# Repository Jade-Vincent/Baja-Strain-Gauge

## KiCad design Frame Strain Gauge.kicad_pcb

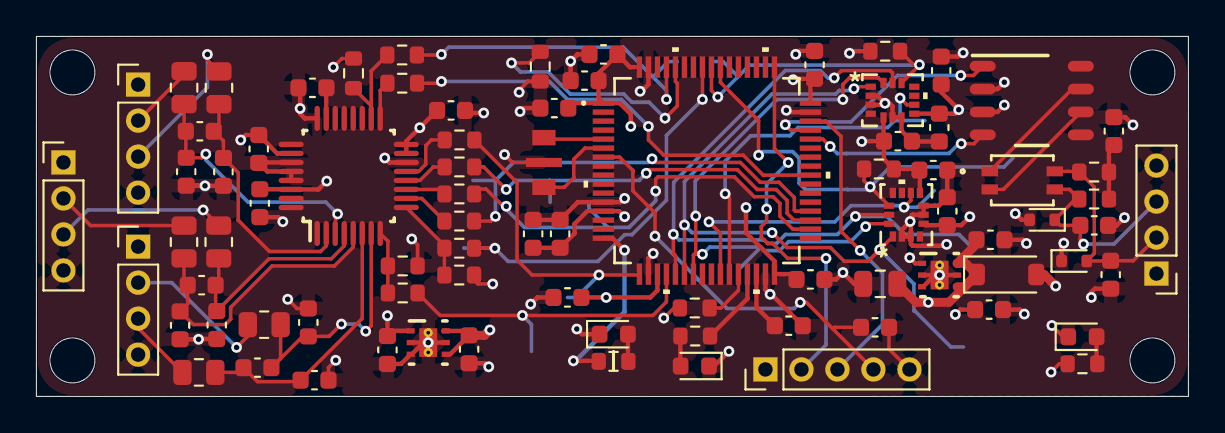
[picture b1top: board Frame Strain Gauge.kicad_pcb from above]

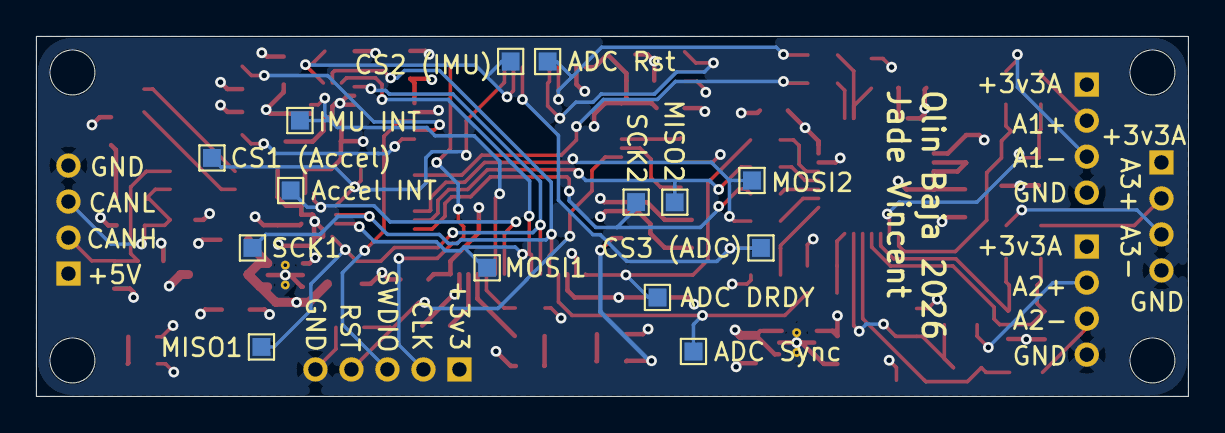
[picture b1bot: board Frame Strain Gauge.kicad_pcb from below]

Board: 4 copper layers, 64.0 x 20.0 mm, 96 parts (14 on the bottom side), 61 nets.

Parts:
ADC DRDY: TestPoint; TestPoint_Pad_1.0x1.0mm
ADC Rst: TestPoint; TestPoint_Pad_1.0x1.0mm
ADC Sync: TestPoint; TestPoint_Pad_1.0x1.0mm
Accel INT: TestPoint; TestPoint_Pad_1.0x1.0mm
C1, C2, C3, C4, C19: 100nF; C_0603_1608Metric
C5: 330 nF; C_0603_1608Metric
C6, C7, C11: 0.1uF; C_0603_1608Metric
C8, C9, C10, C12, C13, C14: 0.01uF; C_0603_1608Metric
C15: 0.1 uF; C_0603_1608Metric
C16, C34, C37, C38, C46, C47, C48, C49: 100 nF; C_0603_1608Metric
C17, C35, C36, C43: 1 uF; C_0603_1608Metric
C18, C33, C44: 2.2 uF; C_0603_1608Metric
C31: 4.7 uF; C_0603_1608Metric
C40, C41: 10 pF; C_0603_1608Metric
C42: 4.7 nF; C_0603_1608Metric
C45: 10 uF; C_0805_2012Metric
CS1 (Accel), CS2 (IMU), CS3 (ADC): TestPoint; TestPoint_Pad_1.0x1.0mm
D1, D2, D3: LED; LED_0603_1608Metric
D4, D5: 12v; D_SOD-523
D6: D_Schottky; D_SOD-123
IMU INT: TestPoint; TestPoint_Pad_1.0x1.0mm
J1: Conn_01x05_Pin; PinHeader_1x05_P2.00mm_Vertical
J4: CAN Header; PinHeader_1x04_P2.00mm_Vertical
J5: Strain Gauge 3 (Shear); PinHeader_1x04_P2.00mm_Vertical
J6: Strain Gauge 2 (Torsion); PinHeader_1x04_P2.00mm_Vertical
J7: Strain Gauge 1 (Axial Load); PinHeader_1x04_P2.00mm_Vertical
MISO1, MISO2: TestPoint; TestPoint_Pad_1.0x1.0mm
MOSI1, MOSI2: TestPoint; TestPoint_Pad_1.0x1.0mm
R1, R2, R5, R6, R7, R8, R9: 10k; R_0603_1608Metric
R10, R17, R18, R19, R20, R21, R22, R28: 47; R_0603_1608Metric
R11, R12, R13, R14, R15, R16: 500; R_0805_2012Metric
R23, R24, R25: 680; R_0603_1608Metric
R26, R27: 60; R_0603_1608Metric
SCK1, SCK2: TestPoint; TestPoint_Pad_1.0x1.0mm
U1: CSTNE8M00GH5C000R0; CSTN_CAP_3P2X1P3_MUR
U2: LSM6DSOXTR; LGA-14L_STM
U3: IIS3DWBTR; LGA-14L_2P5X3X0P83_STM
U4: ADS124S08IPBSR; PBS0032A_N
U5, U8: TPS7A2633DRVR; DRV0006A
U6: TCAN332GDR; D0008A_N
U7: ACT1210-510-2P-TL00; CHOKE_10-2P-TL00_TDK
U10: STM32F412RGT6; LQFP64-10x10mm

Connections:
+3V3: C1.1, C2.1, C3.1, C4.1, C15.2, C18.1, C19.1, C31.1, C34.2, C35.2, C38.1, C46.1, C47.1, C48.1, C49.1, J1.1, R1.2, R5.1, R6.1, R9.1, R23.2, U2.5 (VDDIO), U2.8 (VDD), U3.5 (VDD_IO), U3.8 (VDD), U4.15 (IOVDD), U4.16 (DVDD), U5.1 (OUT), U6.3 (VCC), U10.1 (VBAT), U10.13 (VDDA/VREF+), U10.19 (VDD), U10.32 (VDD), U10.48 (VDD), U10.64 (VDD)
+3V3A: C5.2, C16.1, C44.1, J5.1, J6.1, J7.1, U4.26 (AVDD), U4.30 (REFP0), U8.1 (OUT)
+5V: C17.1, C43.1, C45.2, D6.1 (K), U5.4 (EN), U5.6 (IN), U8.4 (EN), U8.6 (IN)
/Axial+: J7.2, R11.1
/Axial-: J7.3, R12.1
/CAN RXD: U6.4 (RXD), U10.44 (PA11)
/CAN TXD: U6.1 (TXD), U10.45 (PA12)
/CANH: C40.1, D5.2 (A2), J4.2, R26.1, U7.4
/CANL: C41.1, D4.1 (A1), J4.3, R27.2, U7.3
/CS1 IIS3DWBTR: CS1 (Accel).1 (1_1), R5.2, U3.12 (CS), U10.55 (PB3)
/CS2 LSM6DSOXTR: CS2 (IMU).1 (1_1), R6.2, U2.12 (CS), U10.56 (PB4)
/CS3 ADS124S08IPBSR: CS3 (ADC).1 (1_1), R20.1, U10.57 (PB5)
/DRDY ADS124S08IPBSR: ADC DRDY.1 (1_1), R18.1, U10.17 (PA3)
/INT IIS3DWBTR: Accel INT.1 (1_1), U3.9 (INT2), U10.26 (PB0)
/INT LSM6DSOXTR: IMU INT.1 (1_1), U2.9 (INT2), U10.27 (PB1)
/MCO: R28.1, U10.40 (PC9)
/NRST: C37.1, J1.4, U10.7 (NRST)
/Reset ADS124S08IPBSR: ADC Rst.1 (1_1), R10.1, U10.61 (PB8)
/Resonator Input: U1.1, U10.5 (PH0-OSC_IN)
/Resonator Output: U1.3, U10.6 (PH1)
/SPI 1 MISO: MISO1.1 (1_1), U2.1 (SDO/SA0), U3.1 (SDO/SA0), U10.22 (PA6)
/SPI 1 MOSI: MOSI1.1 (1_1), U2.14 (SDA), U3.14 (SDI/SDO/SDA), U10.23 (PA7)
/SPI 1 SCK: SCK1.1 (1_1), U2.13 (SCL), U3.13 (SPC/SCL), U10.21 (PA5)
/SPI 2 MISO: MISO2.1 (1_1), R19.1, U10.35 (PB14)
/SPI 2 MOSI: MOSI2.1 (1_1), R21.1, U10.36 (PB15)
/SPI 2 SCK: R22.1, SCK2.1 (1_1), U10.34 (PB13)
/SWCLK: J1.2, U10.49 (PA14)
/SWDIO: J1.3, U10.46 (PA13)
/Shear+: J5.2, R15.1
/Shear-: J5.3, R16.1
/Start/Sync ADS124S08IPBSR: ADC Sync.1 (1_1), R17.1, U10.20 (PA4)
/Torsion+: J6.2, R13.1
/Torsion-: J6.3, R14.1
GND: C1.2, C2.2, C3.2, C4.2, C5.1, C8.2, C9.1, C10.1, C12.2, C13.1, C14.2, C15.1, C16.2, C17.2, C18.2, C19.2, C31.2, C33.2, C34.1, C35.1, C36.2, C37.2, C38.2, C40.2, C41.2, C42.2, C43.2, C44.2, C45.1, C46.2, C47.2, C48.2, C49.2, D1.1 (K), D2.1 (K), D3.1 (K), D4.2 (A2), D5.1 (A1), J1.5, J4.4, J5.4, J6.4, J7.4, R2.2, R7.2, R8.1, U1.2, U2.2 (SDX), U2.3 (SCX), U2.6 (GND), U2.7 (GND), U3.2 (RES), U3.3 (RES), U3.6 (GND), U3.7 (GND), U4.14 (DGND), U4.24 (REFCOM), U4.27 (AVSS), U4.28 (AVSS-SW), U4.29 (REFN0), U5.2 (FB_NC), U5.3 (PG), U5.5 (GND), U5.7 (PAD), U5.V, U6.2 (GND), U8.2 (FB_NC), U8.3 (PG), U8.5 (GND), U8.7 (PAD), U8.V, U10.12 (VSSA/VREF-), U10.18 (VSS), U10.31 (VSS), U10.47 (VSS), U10.63 (VSS)
unnamed: C42.1, R26.2, R27.1
unnamed: D1.2 (A), R25.2
unnamed: D2.2 (A), R24.1
unnamed: D3.2 (A), R23.1
unnamed: D6.2 (A), J4.1
unnamed: C6.1, C9.2, R11.2, U4.7 (AIN0)
unnamed: C6.2, C8.1, R12.2, U4.6 (AIN1)
unnamed: C10.2, C11.1, R15.2, U4.5 (AIN2)
unnamed: C11.2, C12.1, R16.2, U4.4 (AIN3)
unnamed: C7.1, C13.2, R13.2, U4.3 (AIN4)
unnamed: C7.2, C14.1, R14.2, U4.2 (AIN5)
unnamed: R28.2, U4.17 (CLK)
unnamed: R9.2, R20.2, U4.9 (CS_N)
unnamed: R21.2, U4.10 (DIN)
unnamed: R19.2, U4.12 (DOUT_DRDY_N)
unnamed: R18.2, U4.13 (DRDY_N)
unnamed: C36.1, U4.23 (REFOUT)
unnamed: R1.1, R10.2, U4.18 (RESET_N)
unnamed: R22.2, U4.11 (SCLK)
unnamed: R2.1, R17.2, U4.8 (START_SYNC)
unnamed: U6.7 (CANH), U7.1
unnamed: U6.6 (CANL), U7.2
unnamed: R7.1, U10.60 (BOOT0)
unnamed: R25.1, U10.16 (PA2)
unnamed: R8.2, U10.28 (PB2)
unnamed: R24.2, U10.29 (PB10)
unnamed: C33.1, U10.30 (VCAP_1)
